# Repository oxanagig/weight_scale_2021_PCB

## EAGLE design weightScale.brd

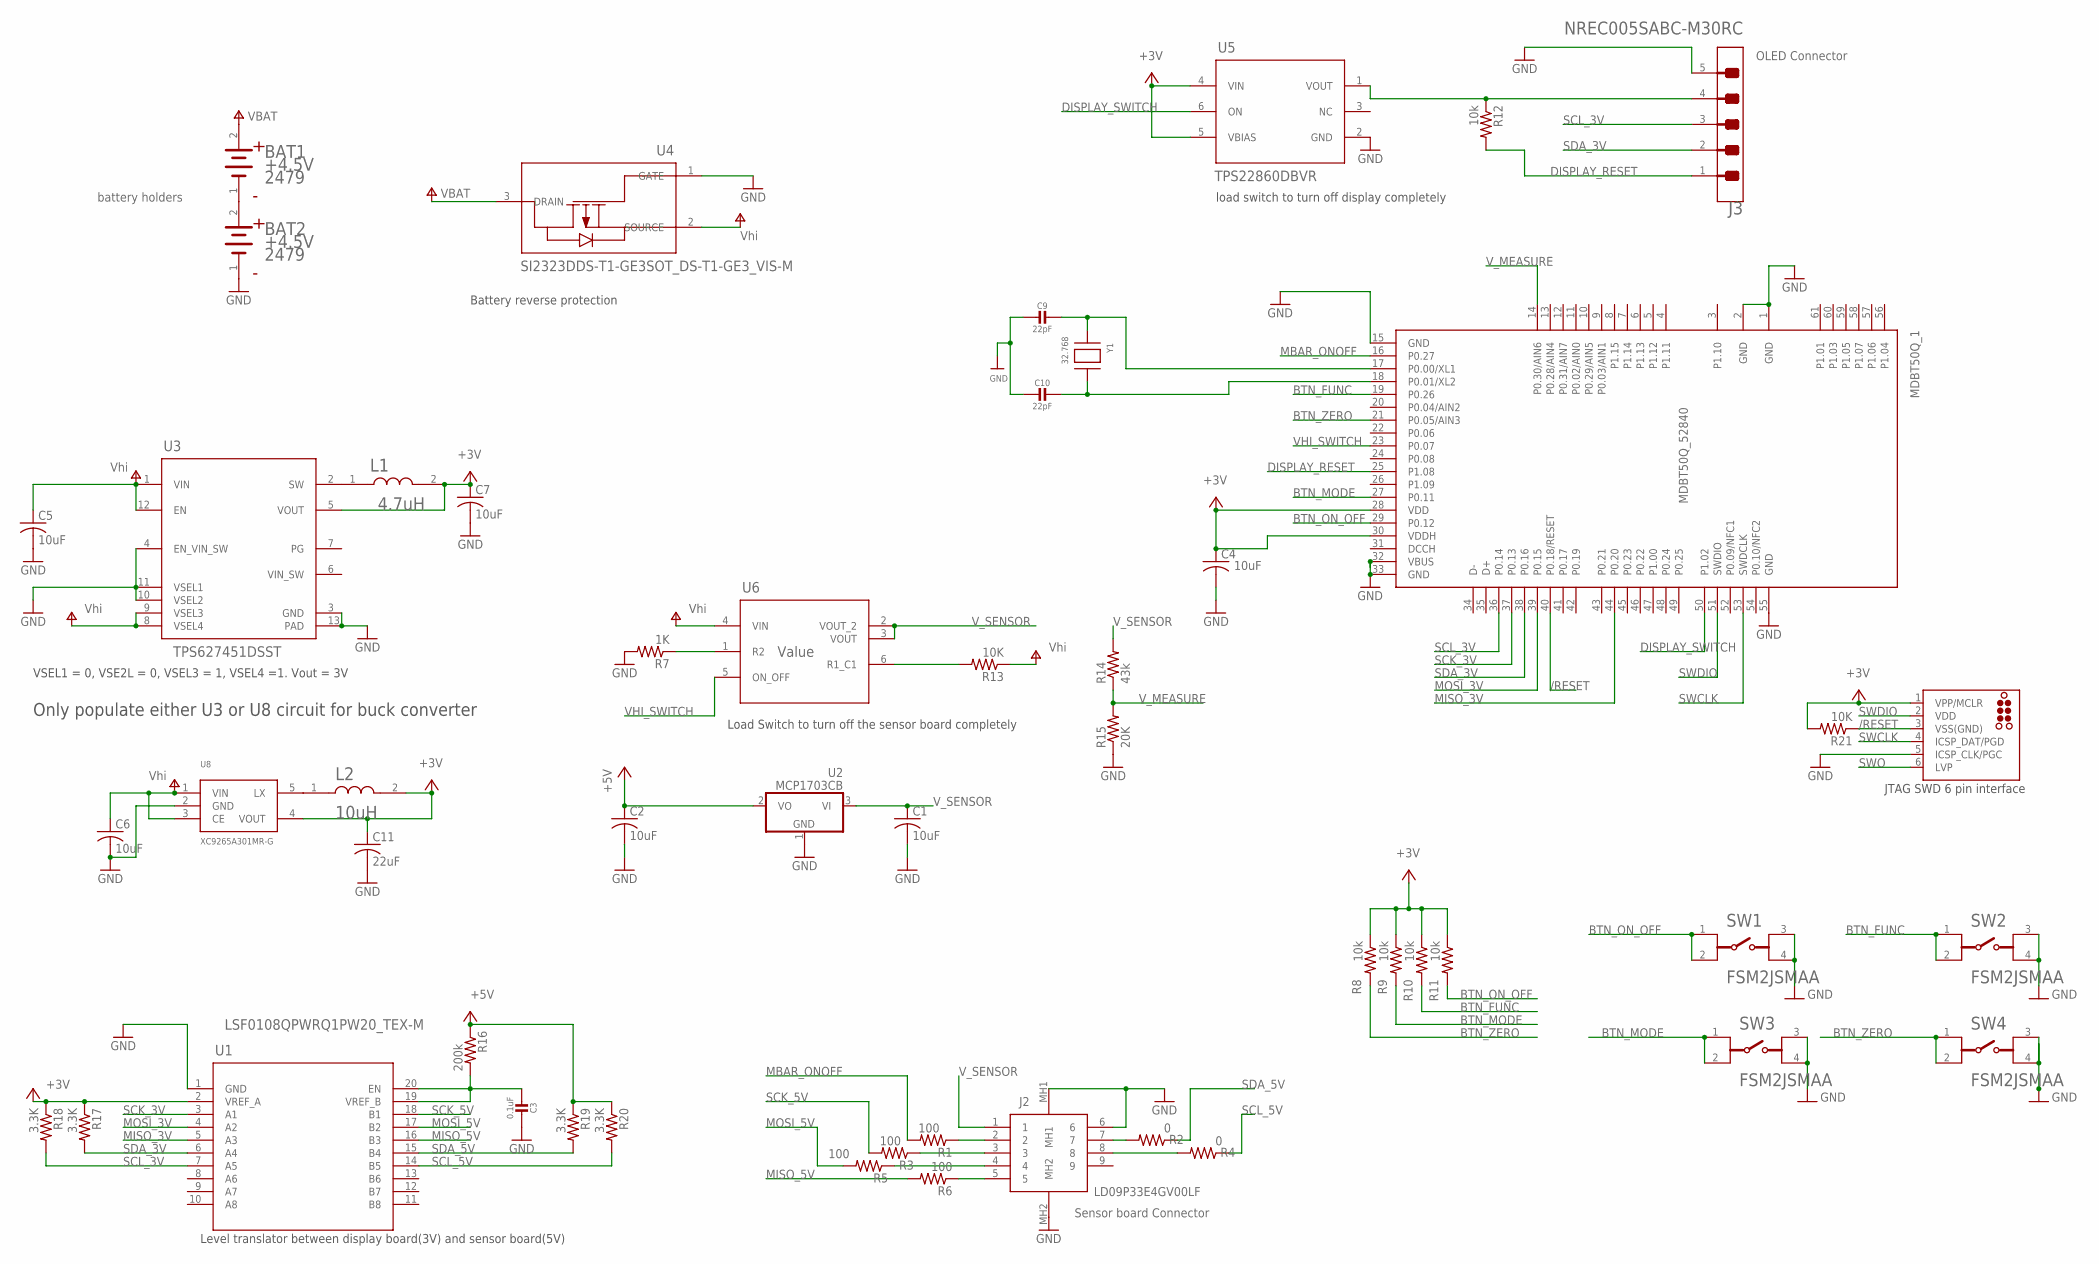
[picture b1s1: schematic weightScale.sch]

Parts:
BAT1, BAT2: KEYSTONE_2479KEYSTONE_2479_0_0; KEYSTONE_2479_0
C1, C2, C5, C7: 10uF; C0805
C3: 0.1uF; _0603MP
C4: 10uF; C1206
C6: 10uF; C0603K
C9, C10: 22pF; _0603MP
C11: 22uF; C0603K
J2: LD09P33E4GV00LF
J3: SULLINS_NREC005SABC-M30RCSULLINS_NREC005SABC-M30R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; SULLINS_NREC005SABC-M30RC_0
J4: TC2030-MCP-NL
L1: MURATA_DFE252010F-4R7M=P2MURATA_DFE252010F-4R7M=P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; MURATA_DFE252010F-4R7M=P2_0
L2: MURATA_1239AS-H-100M=P2MURATA_1239AS-H-100M=P2_0_0; MURATA_1239AS-H-100M=P2_0
MDBT50Q_1: MDBT50Q_52840; MDBT50Q
R1, R3, R5, R6: 100; R0603
R2, R4: 0; R0603
R7: 1K; R0603
R8, R9, R10, R11, R12: 10k; R0603
R13, R21: 10K; R0603
R14: 43k; R0603
R15: 20K; R0603
R16: 200k; R0603
R17, R18, R19, R20: 3.3K; R0603
SW1, SW2, SW3, SW4: TE_CONNECTIVITY_FSM2JSMAATE_CONNECTIVITY_FSM2JSMA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; TE_CONNECTIVITY_FSM2JSMAA_0
U1: LSF0108QPWRQ1PW20_TEX-M; PW20_TEX-M
U2: MCP1703CB; SOT23
U3: TPS627451DSST; DSS0012A
U4: SI2323DDS-T1-GE3SOT_DS-T1-GE3_VIS-M; SOT_DS-T1-GE3_VIS-M
U5: TPS22860DBVR; DBV0006A_N
U6: Value; DDC0006A_N
U8: XC9265A301MR-G; SOT-25
Y1: 32.768; XTAL3215

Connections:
+3V: C4.1, C7.1, C11.1, J4.1 (VPP/MCLR), L1.2, L2.2, MDBT50Q_1.28 (VDD), MDBT50Q_1.30 (VDDH), R8.1, R9.1, R10.1, R11.1, R17.1, R18.1, R21.2, U1.2 (VREF_A), U3.5 (VOUT), U5.4 (VIN), U5.5 (VBIAS), U8.4 (VOUT)
+5V: C2.1, R16.1, R19.1, R20.1, U2.2 (VO)
/RESET: J4.3 (VSS(GND)), MDBT50Q_1.40 (P0.18/RESET), R21.1
BTN_FUNC: MDBT50Q_1.19 (P0.26), R10.2, SW2.1, SW2.2
BTN_MODE: MDBT50Q_1.27 (P0.11), R9.2, SW3.1, SW3.2
BTN_ON_OFF: MDBT50Q_1.29 (P0.12), R11.2, SW1.1, SW1.2
BTN_ZERO: MDBT50Q_1.21 (P0.05/AIN3), R8.2, SW4.1, SW4.2
DISPLAY_RESET: J3.1, MDBT50Q_1.25 (P1.08), R12.2
DISPLAY_SWITCH: MDBT50Q_1.50 (P1.02), U5.6 (ON)
GND: BAT2.1 (CATHODE), C1.2, C2.2, C3.1, C4.2, C5.2, C6.2, C7.2, C9.2, C10.2, C11.2, J2.6, J2.MH1, J2.MH2, J3.5, J4.5 (ICSP_CLK/PGC), MDBT50Q_1.1 (GND), MDBT50Q_1.2 (GND), MDBT50Q_1.15 (GND), MDBT50Q_1.32 (VBUS), MDBT50Q_1.33 (GND), MDBT50Q_1.55 (GND), R7.2, R15.1, SW1.3, SW1.4, SW2.3, SW2.4, SW3.3, SW3.4, SW4.3, SW4.4, U1.1 (GND), U2.1 (GND), U3.3 (GND), U3.4 (EN_VIN_SW), U3.10 (VSEL2), U3.11 (VSEL1), U3.13 (PAD), U4.1 (GATE), U5.2 (GND), U8.2 (GND)
MBAR_ONOFF: MDBT50Q_1.16 (P0.27), R1.2
MISO_3V: MDBT50Q_1.44 (P0.20), U1.5 (A3)
MISO_5V: R6.2, U1.16 (B3)
MOSI_3V: MDBT50Q_1.39 (P0.15), U1.4 (A2)
MOSI_5V: R5.2, U1.17 (B2)
unnamed: R7.1, U6.1 (R2)
unnamed: J2.2, R1.1
unnamed: R13.2, U6.6 (R1_C1)
unnamed: J2.3, R3.1
unnamed: J2.7, R2.2
unnamed: C3.2, R16.2, U1.19 (VREF_B), U1.20 (EN)
unnamed: J2.4, R5.1
unnamed: J2.5, R6.1
unnamed: C9.1, MDBT50Q_1.17 (P0.00/XL1), Y1.P$1
unnamed: C10.1, MDBT50Q_1.18 (P0.01/XL2), Y1.P$2
unnamed: J2.8, R4.2
unnamed: J3.4, R12.1, U5.1 (VOUT)
unnamed: L2.1, U8.5 (LX)
unnamed: BAT1.1 (CATHODE), BAT2.2 (ANODE)
unnamed: L1.1, U3.2 (SW)
SCK_3V: MDBT50Q_1.37 (P0.13), U1.3 (A1)
SCK_5V: R3.2, U1.18 (B1)
SCL_3V: J3.3, MDBT50Q_1.36 (P0.14), R18.2, U1.7 (A5)
SCL_5V: R4.1, R20.2, U1.14 (B5)
SDA_3V: J3.2, MDBT50Q_1.38 (P0.16), R17.2, U1.6 (A4)
SDA_5V: R2.1, R19.2, U1.15 (B4)
SWCLK: J4.4 (ICSP_DAT/PGD), MDBT50Q_1.53 (SWDCLK)
SWDIO: J4.2 (VDD), MDBT50Q_1.51 (SWDIO)
SWO: J4.6 (LVP)
V+: BAT1.2 (ANODE), C5.1, C6.1, R13.1, U3.1 (VIN), U3.8 (VSEL4), U3.9 (VSEL3), U3.12 (EN), U4.2 (SOURCE), U4.3 (DRAIN), U6.4 (VIN), U8.1 (VIN), U8.3 (CE)
VHI_SWITCH: MDBT50Q_1.23 (P0.07), U6.5 (ON_OFF)
VIN_SW: U3.6 (VIN_SW)
V_MEASURE: MDBT50Q_1.14 (P0.30/AIN6), R14.1, R15.2
V_SENSOR: C1.1, J2.1, R14.2, U2.3 (VI), U6.2 (VOUT_2), U6.3 (VOUT)

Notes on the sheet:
OLED Connector
Sensor board Connector
battery holders
Battery reverse protection
VSEL1 = 0, VSE2L = 0, VSEL3 = 1, VSEL4 =1. Vout = 3V
JTAG SWD 6 pin interface
Level translator between display board(3V) and sensor board(5V)
Load Switch to turn off the sensor board completely
load switch to turn off display completely
Only populate either U3 or U8 circuit for buck converter

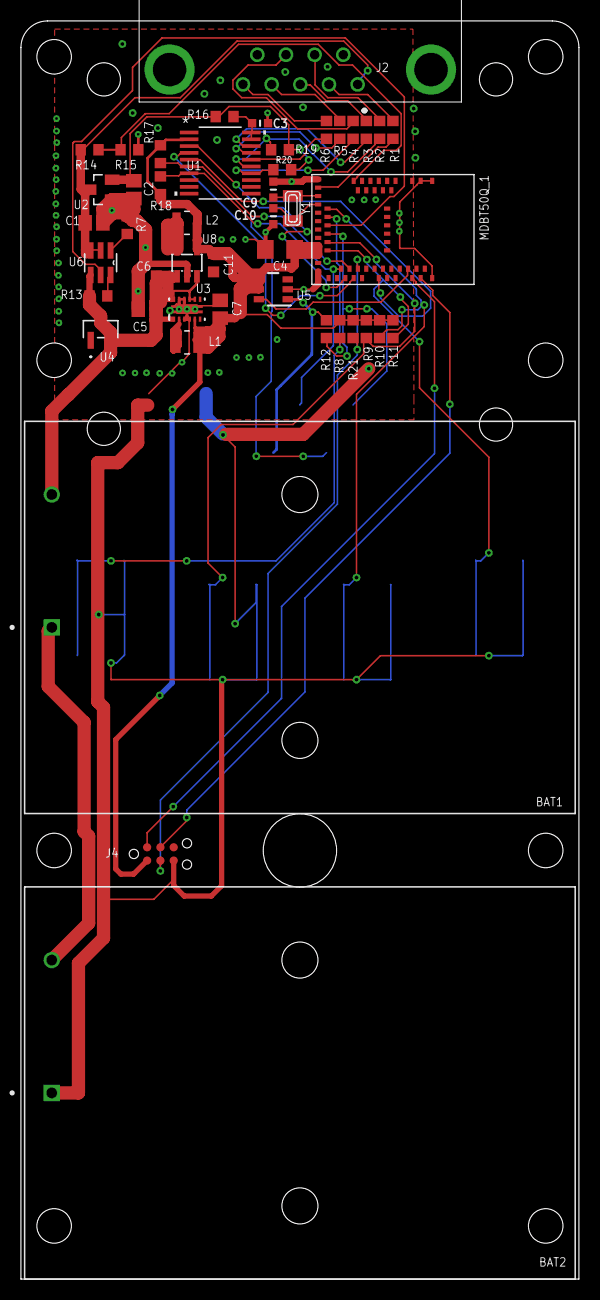
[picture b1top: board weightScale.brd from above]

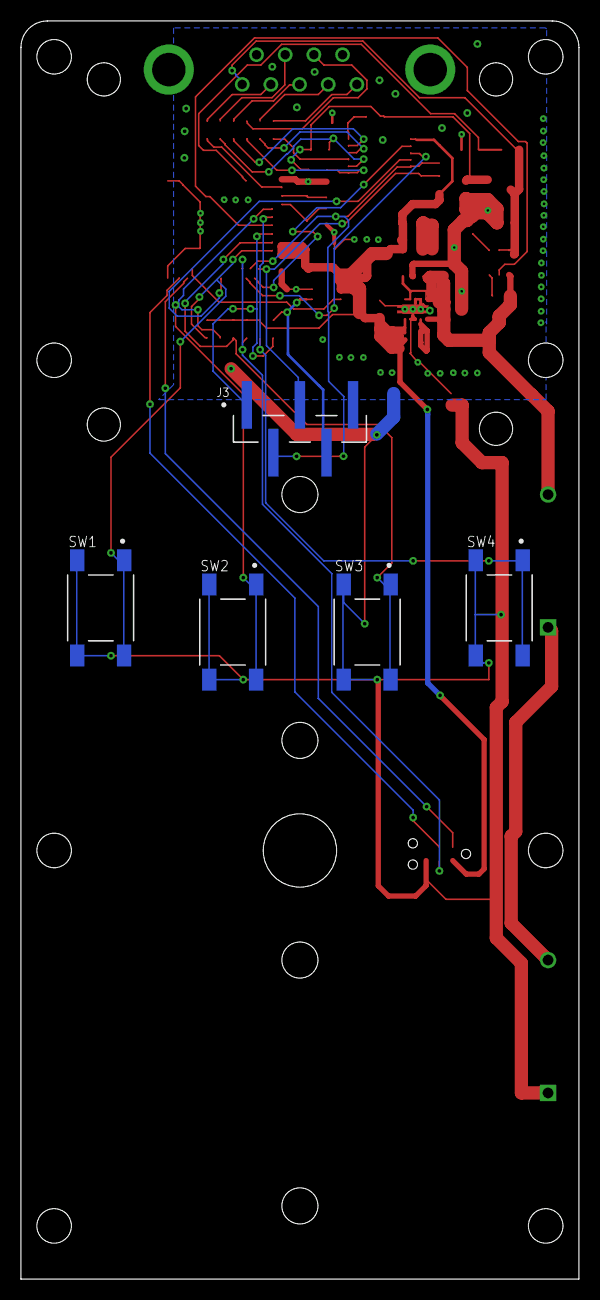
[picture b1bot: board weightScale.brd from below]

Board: 2 copper layers, 53.3 x 120.3 mm, 51 parts (5 on the bottom side), 42 nets.

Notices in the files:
parts and their libraries:
microbuilder: This work is placed in the public domain, and may be freely used for commercial and non-commercial work with the following conditions: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
tag-connect: ©2009 ROFA.cz - modified and updated by Robert Darlington ‹rdarlington@gmail.com›
